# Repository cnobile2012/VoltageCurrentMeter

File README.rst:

*********************
Voltage Current Meter
*********************
The MIT License (MIT)

A circuit to show voltage and current on a TFT display. Parts can be added
using a small array of mounting holes on the board, plus two daughter boards
can be plugged into female connectors. There is an on board 5V to 3.3V
regulator which powers all components.

=====
KiCAD
=====

KiCAD files of the schematic and PCB.

==================
Setup Instructions
==================

  1. J1 - J8 are JST 1.5mm 3-pin connectors and are for the analog inputs or
     outputs of the 74HC4051 (8-Channel Analog Multiplexer/Demultiplexer).
  2. J9 is a screw terminal block for the circuits supply voltage.
  3. J10 is the Power Jumper. It allows the use of 5V on J9 or routes the
     V-IN on J9 to  a daughter board which can convert the voltage on J9 to 5V.
  4. J11 is a 4 pin standard female socket for the optional Daughter Board 1.
     This board can be used for external circuitry to convert any voltage to
     the 5 volts needed by the 3.3V regulator.
  5. J12 is a 12 pin standard female socket that provides the 2nd daughter
     board with all the control pins from the 74HC4051. It also provides the
     two pins not used on the Seeeduino XIAO plus ground and 3.3V power.

==============
PCBs Version 1
==============

=========
Schematic
=========

.. image:: images/VoltageCurrentMeter-V1.0.png
  :width: 800
  :alt: Schematic

================
Arduino Sketches
================

Below are the sketches that use this board.

--------------
BatteryCharger
--------------

This sketch displays the set voltage and current limited values and the actual
values while charging Li-Ion batteries. The charging voltage is adjustable to
12.6V (3 cells), 16.8V (4 cells), or 21.0V (5 cells) depending on the number of
cells. The default current is limited to 1250mA or can be set to adjustable
using a potentiometer.

Feel free to contact me at: carl dot nobile at gmail.com

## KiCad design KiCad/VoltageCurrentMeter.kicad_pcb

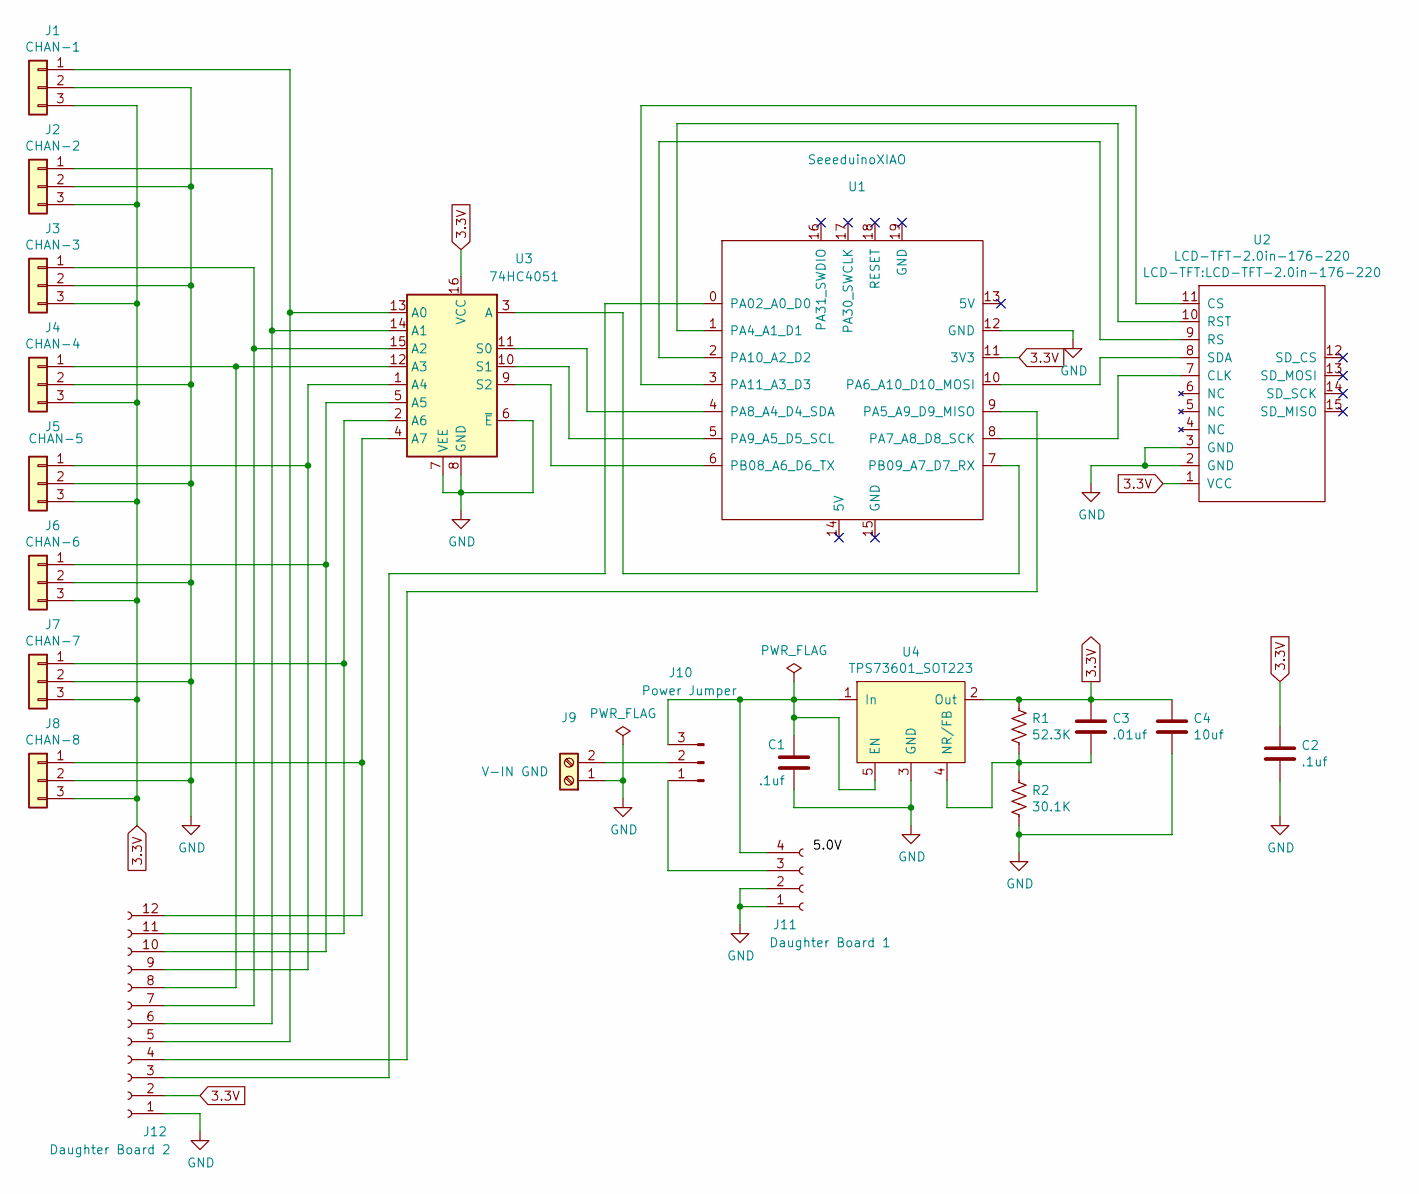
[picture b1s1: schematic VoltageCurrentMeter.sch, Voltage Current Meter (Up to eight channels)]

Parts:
C1, C2: .1uf; C_Disc_D4.7mm_W2.5mm_P5.00mm
C3: .01uf; C_Disc_D4.7mm_W2.5mm_P5.00mm
C4: 10uf; CP_Radial_D6.3mm_P2.50mm
J1: CHAN-1; JST_CJN_1x03_P1.50mm_Vertical
J2: CHAN-2; JST_CJN_1x03_P1.50mm_Vertical
J3: CHAN-3; JST_CJN_1x03_P1.50mm_Vertical
J4: CHAN-4; JST_CJN_1x03_P1.50mm_Vertical
J5: CHAN-5; JST_CJN_1x03_P1.50mm_Vertical
J6: CHAN-6; JST_CJN_1x03_P1.50mm_Vertical
J7: CHAN-7; JST_CJN_1x03_P1.50mm_Vertical
J8: CHAN-8; JST_CJN_1x03_P1.50mm_Vertical
J9: V-IN GND; TerminalBlock_Phoenix_MKDS-1,5-2-5.08_1x02_P5.08mm_Horizont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
J10: Power Jumper; PinHeader_1x03_P2.54mm_Vertical
J11: Daughter Board 1; PinSocket_1x04_P2.54mm_Vertical
J12: Daughter Board 2; PinSocket_1x12_P2.54mm_Vertical
R1: 52.3K; R_Axial_DIN0207_L6.3mm_D2.5mm_P10.16mm_Horizontal
R2: 30.1K; R_Axial_DIN0207_L6.3mm_D2.5mm_P10.16mm_Horizontal
U1: SeeeduinoXIAO; SeeeduinoXIAO-MOUDLE14P-2.54-21X17.8MM
U2: LCD-TFT-2.0in-176-220
U3: 74HC4051; SO-16_3.9x9.9mm_P1.27mm
U4: TPS73601_SOT223; SOT-223-6_TabPin3

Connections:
3.3V: C2.1, C3.1, C4.1, J1.3, J2.3, J3.3, J4.3, J5.3, J6.3, J7.3, J8.3, J12.2, R1.1, U1.11 (3V3), U2.1 (VCC), U3.16 (VCC), U4.2 (Out)
GND: C1.2, C2.2, C4.2, J1.2, J2.2, J3.2, J4.2, J5.2, J6.2, J7.2, J8.2, J9.1, J11.1, J11.2, J12.1, R2.2, U1.12 (GND), U2.2 (GND), U2.3 (GND), U3.6 (~E), U3.7 (VEE), U3.8 (GND), U4.3 (GND)
unnamed: C1.1, J10.3, J11.4, U4.1 (In), U4.5 (EN)
unnamed: C3.2, R1.2, R2.1, U4.4 (NR/FB)
unnamed: J1.1, J12.5, U3.13 (A0)
unnamed: J10.1, J11.3
unnamed: J9.2, J10.2
unnamed: J12.3, U1.0 (PA02_A0_D0)
unnamed: J12.4, U1.9 (PA5_A9_D9_MISO)
unnamed: J2.1, J12.6, U3.14 (A1)
unnamed: J3.1, J12.7, U3.15 (A2)
unnamed: J4.1, J12.8, U3.12 (A3)
unnamed: J5.1, J12.9, U3.1 (A4)
unnamed: J6.1, J12.10, U3.5 (A5)
unnamed: J7.1, J12.11, U3.2 (A6)
unnamed: J8.1, J12.12, U3.4 (A7)
unnamed: U1.1 (PA4_A1_D1), U2.10 (RST)
unnamed: U1.2 (PA10_A2_D2), U2.9 (RS)
unnamed: U1.3 (PA11_A3_D3), U2.11 (CS)
unnamed: U1.4 (PA8_A4_D4_SDA), U3.11 (S0)
unnamed: U1.5 (PA9_A5_D5_SCL), U3.10 (S1)
unnamed: U1.6 (PB08_A6_D6_TX), U3.9 (S2)
unnamed: U1.7 (PB09_A7_D7_RX), U3.3 (A)
unnamed: U1.8 (PA7_A8_D8_SCK), U2.7 (CLK)
unnamed: U1.10 (PA6_A10_D10_MOSI), U2.8 (SDA)

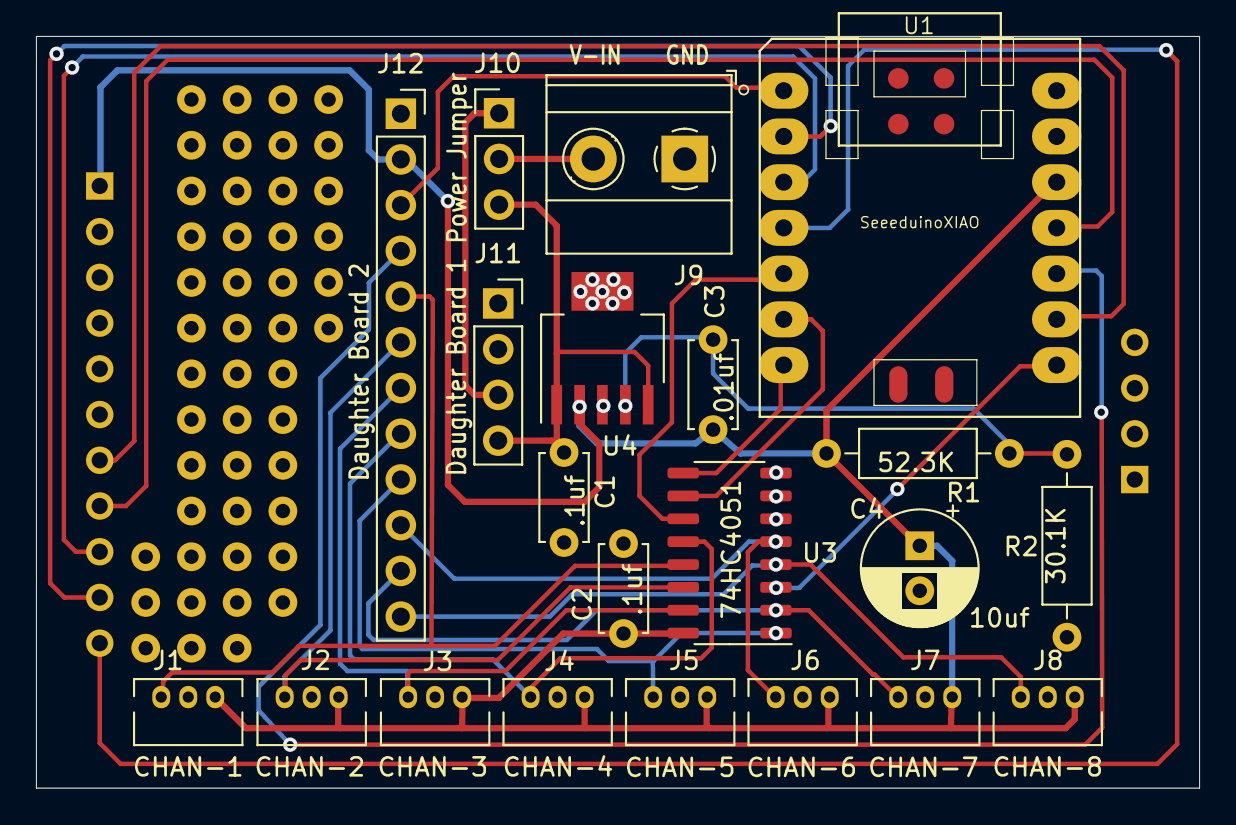
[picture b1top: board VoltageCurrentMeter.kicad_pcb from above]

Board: 2 copper layers, 64.6 x 41.8 mm, 22 parts (1 on the bottom side), 25 nets.

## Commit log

2021-09-12 Initialcommit.
2021-09-13 Updates to schematic and added images and a README.
2021-09-13 Bumped up the schematic width.
2021-09-13 Renamed the gerber files and updated the README.
2021-09-13 Added an Arduino sketch and updated the README.
2021-09-13 Updated the README.
2021-09-13 Updated the gerber files.
2021-09-24 Fixed an issue where the pins on the Seeeduino XIAO were a little too far apart.
